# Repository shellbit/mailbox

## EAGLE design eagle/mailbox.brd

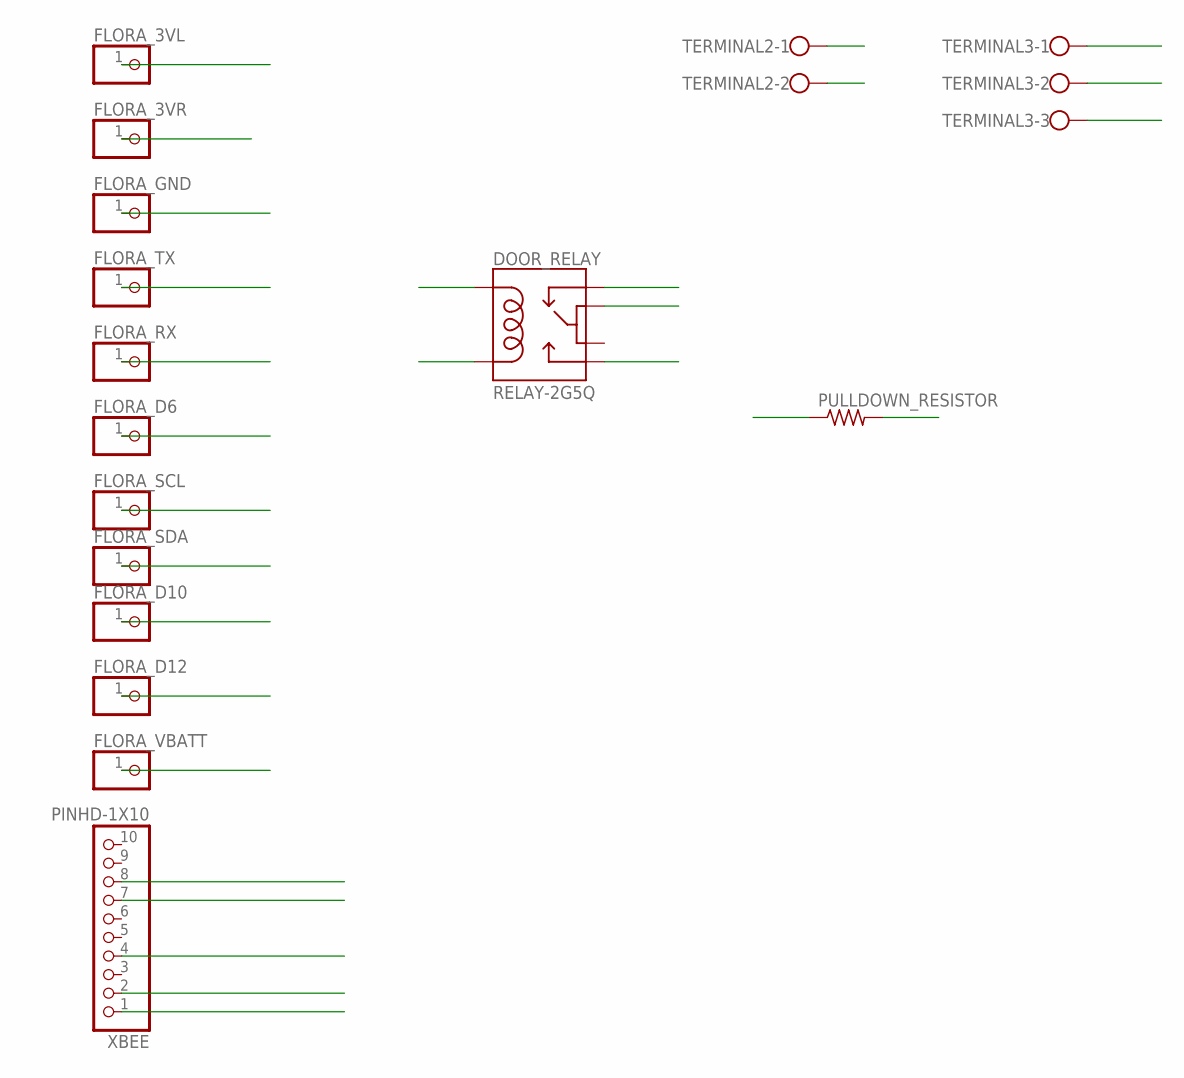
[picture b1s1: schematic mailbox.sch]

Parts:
DOOR_RELAY: RELAY-2G5Q; RELAY-G5V
FLORA_3VL, FLORA_3VR: PINHD-1X1CB; 1X01-CLEANBIG
FLORA_D6, FLORA_D10, FLORA_D12: PINHD-1X1CB; 1X01-CLEANBIG
FLORA_GND: PINHD-1X1CB; 1X01-CLEANBIG
FLORA_RX: PINHD-1X1CB; 1X01-CLEANBIG
FLORA_SCL: PINHD-1X1CB; 1X01-CLEANBIG
FLORA_SDA: PINHD-1X1CB; 1X01-CLEANBIG
FLORA_TX: PINHD-1X1CB; 1X01-CLEANBIG
FLORA_VBATT: PINHD-1X1CB; 1X01-CLEANBIG
PULLDOWN_RESISTOR: FLIPFLOP-RES; 0805-THM
TERMINAL2: W237-102
TERMINAL3: W237-103
XBEE: PINHD-1X10; 1X10-BIG

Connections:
3VL: DOOR_RELAY.1, DOOR_RELAY.2, FLORA_3VL.1
3VR: FLORA_3VR.1, XBEE.1
D6: FLORA_D6.1, TERMINAL3.1
D10: FLORA_D10.1
D12: FLORA_D12.1, PULLDOWN_RESISTOR.1, TERMINAL3.2
DOOR_SWITCH: DOOR_RELAY.9, TERMINAL2.2
GND: DOOR_RELAY.10, FLORA_GND.1, PULLDOWN_RESISTOR.2, TERMINAL2.1, XBEE.4
RX: FLORA_TX.1, XBEE.7
SCL: DOOR_RELAY.5, FLORA_SCL.1
SDA: FLORA_SDA.1, XBEE.2
TX: FLORA_RX.1, XBEE.8
VBATT: FLORA_VBATT.1, TERMINAL3.3

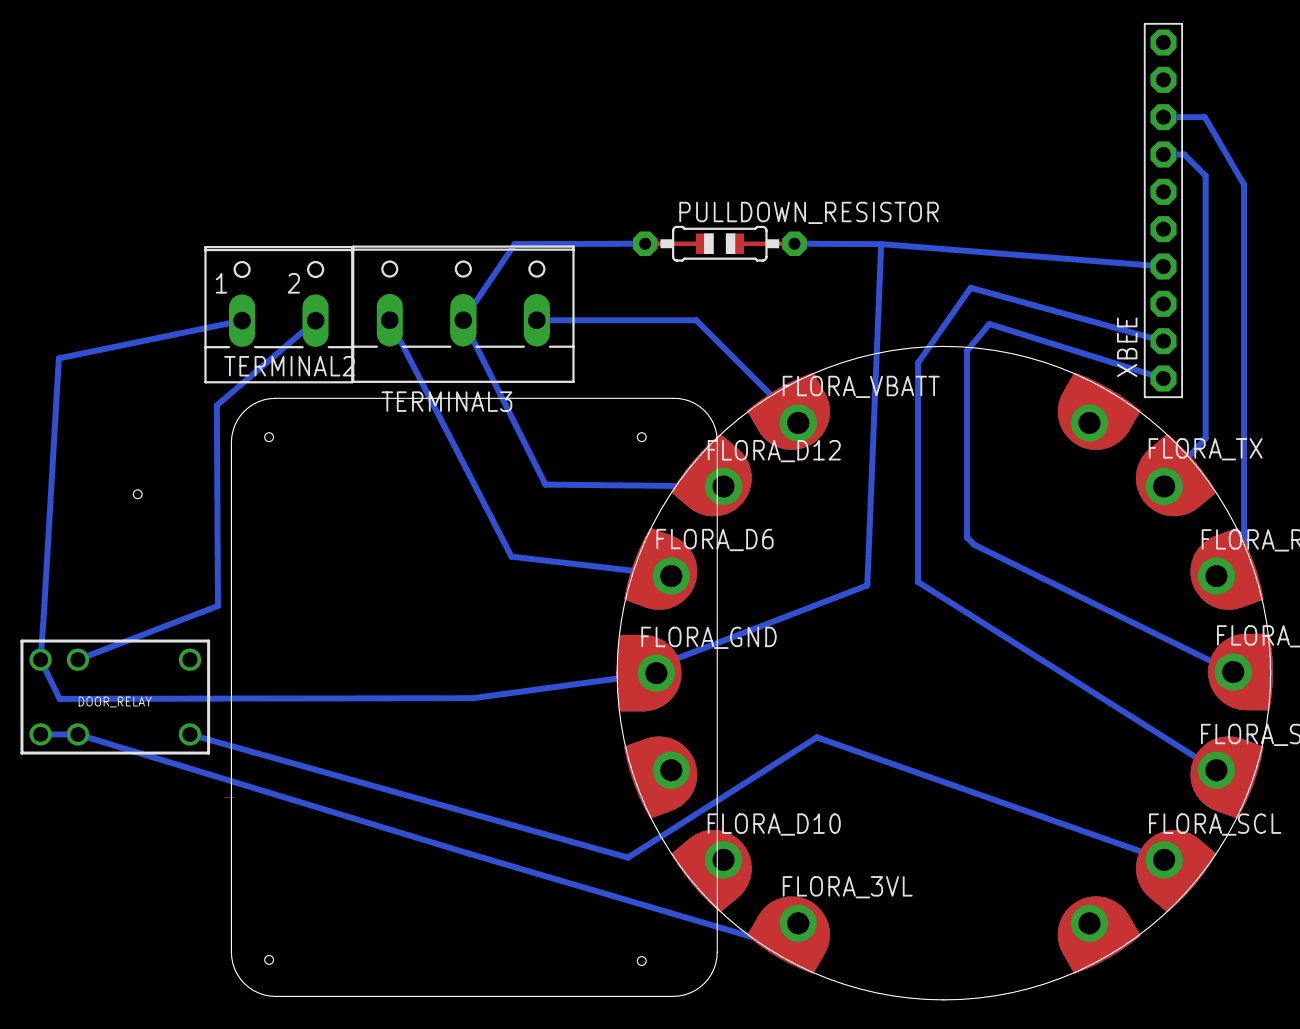
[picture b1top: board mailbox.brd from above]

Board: 2 copper layers, 70.7 x 44.5 mm, 30 parts (0 on the bottom side), 11 nets.

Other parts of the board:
3.3VTAP, 3V3TAP2: SEWTAP-2.0IN; SEWINGTAP_2.0
D6: SEWTAP-2.0IN; SEWINGTAP_2.0
GND3TAP: SEWTAP-2.0IN; SEWINGTAP_2.0
GNDTAP, GNDTAP2: SEWTAP-2.0IN; SEWINGTAP_2.0
IO9, IO10, IO12: SEWTAP-2.0IN; SEWINGTAP_2.0
RX: SEWTAP-2.0IN; SEWINGTAP_2.0
SCL: SEWTAP-2.0IN; SEWINGTAP_2.0
SDA: SEWTAP-2.0IN; SEWINGTAP_2.0
TX: SEWTAP-2.0IN; SEWINGTAP_2.0
VCC2: SEWTAP-2.0IN; SEWINGTAP_2.0

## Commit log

2015-06-15 Added eagle and arduino files

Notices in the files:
parts and their libraries:
SparkFun-Electromechanical: Licensing: Creative Commons ShareAlike 4.0 International - https://creativecommons.org/licenses/by-sa/4.0
